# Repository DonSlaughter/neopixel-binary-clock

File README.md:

# neopixel-binary-clock
Binary clock using Neopixels, ESP8266 and DS3231 real time clock.
I used PlatformIO for this Project. The Arduino IDE will do fine i guess.

# Known Problems
The first LED has some kind of Voltage spikes if WiFi is enabled. The trick is
to Compile this Code that the RTC gets a Timestamp and then Compile this Code
without WiFi. If someone can help with that it would be great, but it works
without WiFi.

# PCB Design

# idea from civ0
https://github.com/civ0/neopixel-binary-clock

## Timezones
Timeszones are changend with Lib 'Timezones.h'
Everything can be changed with TimeChangeRule.

## Parts
* ESP8266 WeemosD1 Mini
* Logic Level Shifter
* DS3231
* 220 Ohm Resistor
* Schottky Diode with low Voltage drop
* 2 x Capacitor 680uF
* Barrel Jack
* Screw Terminal
* 26 x WS2812B SMD Led's

## Connect to Wi-Fi
create a file named secrets.h in the folder src.
it should contain your wifi network (ssid) and your wifi password:
```c
const char *ssid = "";
const char *pass = "";
```
## Code
Code needs to be cleand up

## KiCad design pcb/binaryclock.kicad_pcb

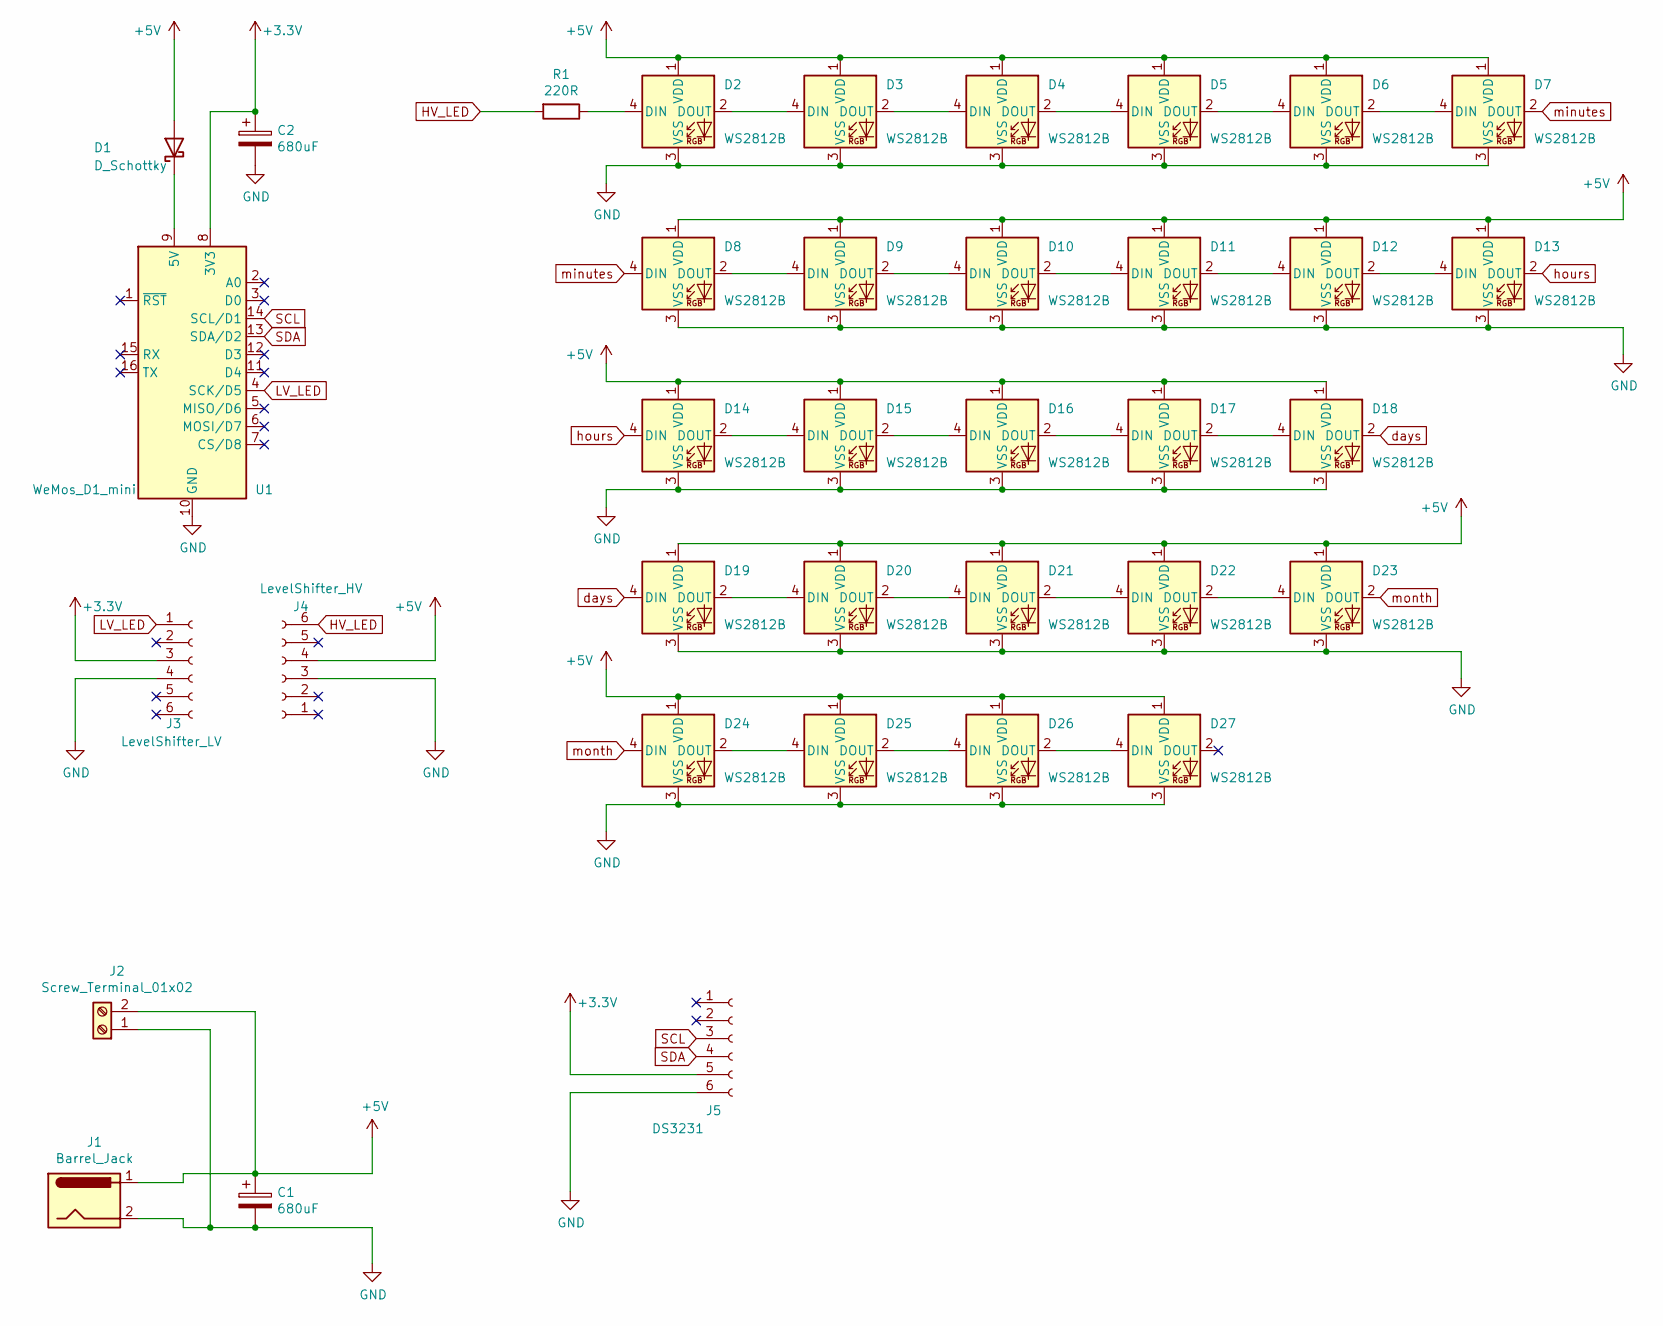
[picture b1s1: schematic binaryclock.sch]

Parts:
C1, C2: 680uF; CP_Radial_D5.0mm_P2.50mm
D1: D_Schottky; D_A-405_P7.62mm_Horizontal
D2, D3, D4, D5, D6, D7, D8, D9, D10, D11, D12, D13, D14, D15, D16, D17, D18, D19, D20, D21, D22, D23, D24, D25, D26, D27: WS2812B; LED_WS2812B_PLCC4_5.0x5.0mm_P3.2mm
J1: Barrel_Jack; BarrelJack_Wuerth_6941xx301002
J2: Screw_Terminal_01x02; TerminalBlock_bornier-2_P5.08mm
J3: LevelShifter_LV; PinSocket_1x06_P2.54mm_Vertical
J4: LevelShifter_HV; PinSocket_1x06_P2.54mm_Vertical
J5: DS3231; PinSocket_1x06_P2.54mm_Vertical
R1: 220R; R_Axial_DIN0207_L6.3mm_D2.5mm_P7.62mm_Horizontal
U1: WeMos_D1_mini; WEMOS_D1_mini_light

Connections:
+3V3: C2.1, J3.3, J5.5, U1.8 (3V3)
+5V: C1.1, D1.2 (A), D2.1 (VDD), D3.1 (VDD), D4.1 (VDD), D5.1 (VDD), D6.1 (VDD), D7.1 (VDD), D8.1 (VDD), D9.1 (VDD), D10.1 (VDD), D11.1 (VDD), D12.1 (VDD), D13.1 (VDD), D14.1 (VDD), D15.1 (VDD), D16.1 (VDD), D17.1 (VDD), D18.1 (VDD), D19.1 (VDD), D20.1 (VDD), D21.1 (VDD), D22.1 (VDD), D23.1 (VDD), D24.1 (VDD), D25.1 (VDD), D26.1 (VDD), D27.1 (VDD), J1.1, J2.2, J4.4
GND: C1.2, C2.2, D2.3 (VSS), D3.3 (VSS), D4.3 (VSS), D5.3 (VSS), D6.3 (VSS), D7.3 (VSS), D8.3 (VSS), D9.3 (VSS), D10.3 (VSS), D11.3 (VSS), D12.3 (VSS), D13.3 (VSS), D14.3 (VSS), D15.3 (VSS), D16.3 (VSS), D17.3 (VSS), D18.3 (VSS), D19.3 (VSS), D20.3 (VSS), D21.3 (VSS), D22.3 (VSS), D23.3 (VSS), D24.3 (VSS), D25.3 (VSS), D26.3 (VSS), D27.3 (VSS), J1.2, J2.1, J3.4, J4.3, J5.6, U1.10 (GND)
HV_LED: J4.6, R1.2
LV_LED: J3.1, U1.4 (SCK/D5)
unnamed: D1.1 (K), U1.9 (5V)
unnamed: D2.2 (DOUT), D3.4 (DIN)
unnamed: D2.4 (DIN), R1.1
unnamed: D3.2 (DOUT), D4.4 (DIN)
unnamed: D4.2 (DOUT), D5.4 (DIN)
unnamed: D5.2 (DOUT), D6.4 (DIN)
unnamed: D6.2 (DOUT), D7.4 (DIN)
unnamed: D8.2 (DOUT), D9.4 (DIN)
unnamed: D10.2 (DOUT), D11.4 (DIN)
unnamed: D9.2 (DOUT), D10.4 (DIN)
unnamed: D11.2 (DOUT), D12.4 (DIN)
unnamed: D12.2 (DOUT), D13.4 (DIN)
unnamed: D14.2 (DOUT), D15.4 (DIN)
unnamed: D15.2 (DOUT), D16.4 (DIN)
unnamed: D16.2 (DOUT), D17.4 (DIN)
unnamed: D17.2 (DOUT), D18.4 (DIN)
unnamed: D19.2 (DOUT), D20.4 (DIN)
unnamed: D20.2 (DOUT), D21.4 (DIN)
unnamed: D21.2 (DOUT), D22.4 (DIN)
unnamed: D22.2 (DOUT), D23.4 (DIN)
unnamed: D24.2 (DOUT), D25.4 (DIN)
unnamed: D25.2 (DOUT), D26.4 (DIN)
unnamed: D26.2 (DOUT), D27.4 (DIN)
SCL: J5.3, U1.14 (SCL/D1)
SDA: J5.4, U1.13 (SDA/D2)
days: D18.2 (DOUT), D19.4 (DIN)
hours: D13.2 (DOUT), D14.4 (DIN)
minutes: D7.2 (DOUT), D8.4 (DIN)
month: D23.2 (DOUT), D24.4 (DIN)

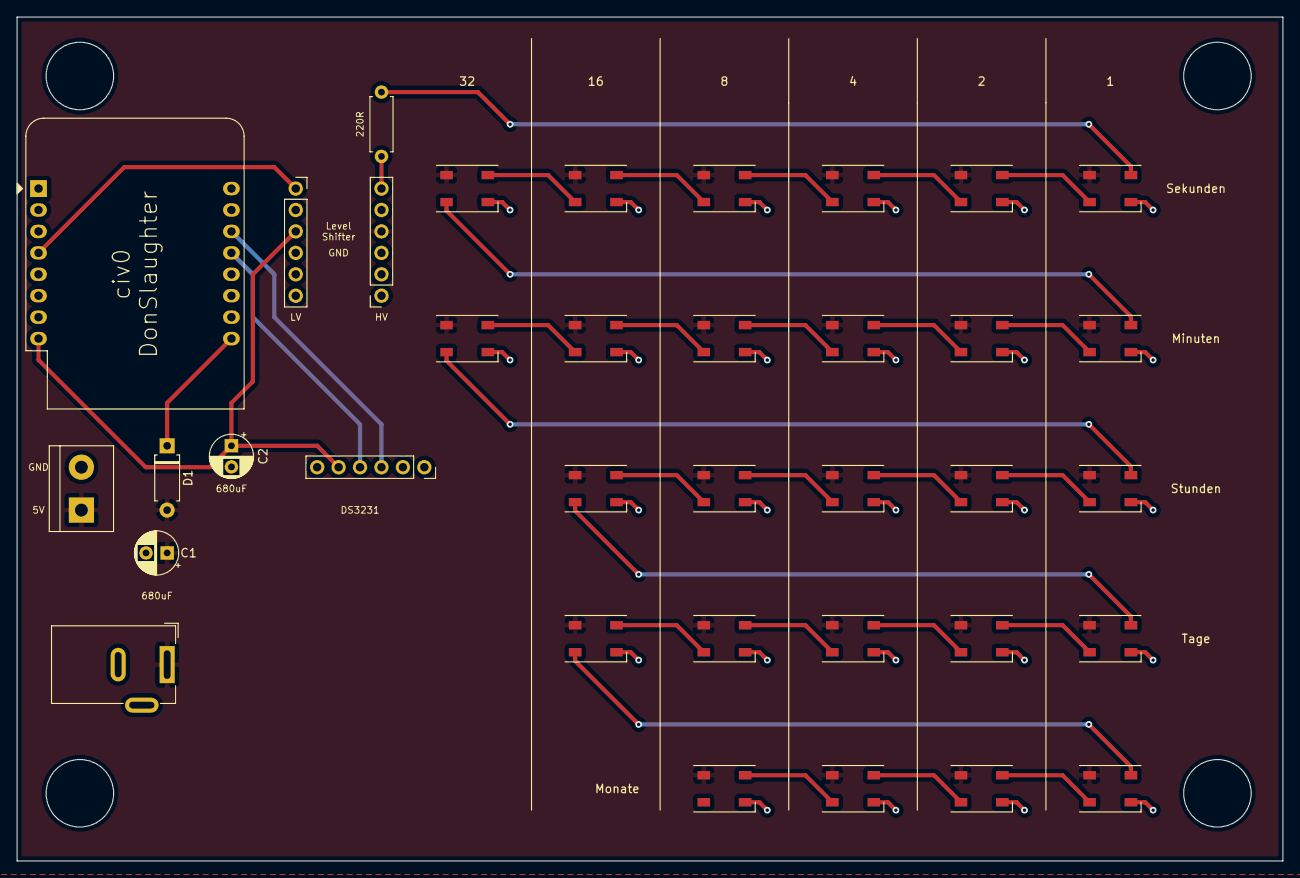
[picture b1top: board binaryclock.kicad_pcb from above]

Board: 2 copper layers, 150.0 x 100.0 mm, 36 parts (0 on the bottom side), 34 nets.

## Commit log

2021-10-08 new folder structure
2021-10-08 only moving into new pio folder structure without changing code
2021-10-08 new pio ini
2021-10-08 gitignore change to exclude secrets.h with ssid and pw
2021-10-08 main and pio gitigne changes
2021-10-10 dont track compile commands
2021-10-10 dont track compile commands_1
2021-10-28 reboot
2021-10-29 working ntp, time and timezone
2021-10-30 clock okai i guess
2021-10-30 working clock, colors and timings needs to be adjusted
2021-10-30 pcb finished
2021-11-04 new readme
2021-11-04 parts added
2021-11-04 parts added _ 1
2021-11-07 fastled didnt work, firstled allways on...
2021-11-07 working with makuna but incompatible with pcb
2021-11-07 readme updated
2021-11-08 still fuckup with 1st led
2021-11-08 working without wifi but led_s allright
2021-11-11 new shift
2021-11-16 working nightmode I hope
2021-11-22 finish i guess
2021-11-30 Problems added to Readme file
